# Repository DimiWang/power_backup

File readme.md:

# Power backup automation for 12V battery.

## Features:
* Fits on DIN rail.
* Power source circuit cut-off when no power
   (saves battery energy when power is not available)
* Measures battery real capacity
* Measures input voltage
* Battery cut-off when discharged
* LED signalisation
* Open collector signal on battery or power fail
* Output 5V max.100mA
* Output from battery
* Arduino pro mini
* Output bistable relay (for energy saving)

## Box enclosure

## Main Board

## Main Board TOP layer

## Main Board BOTTOM layer

## Main Board schematic

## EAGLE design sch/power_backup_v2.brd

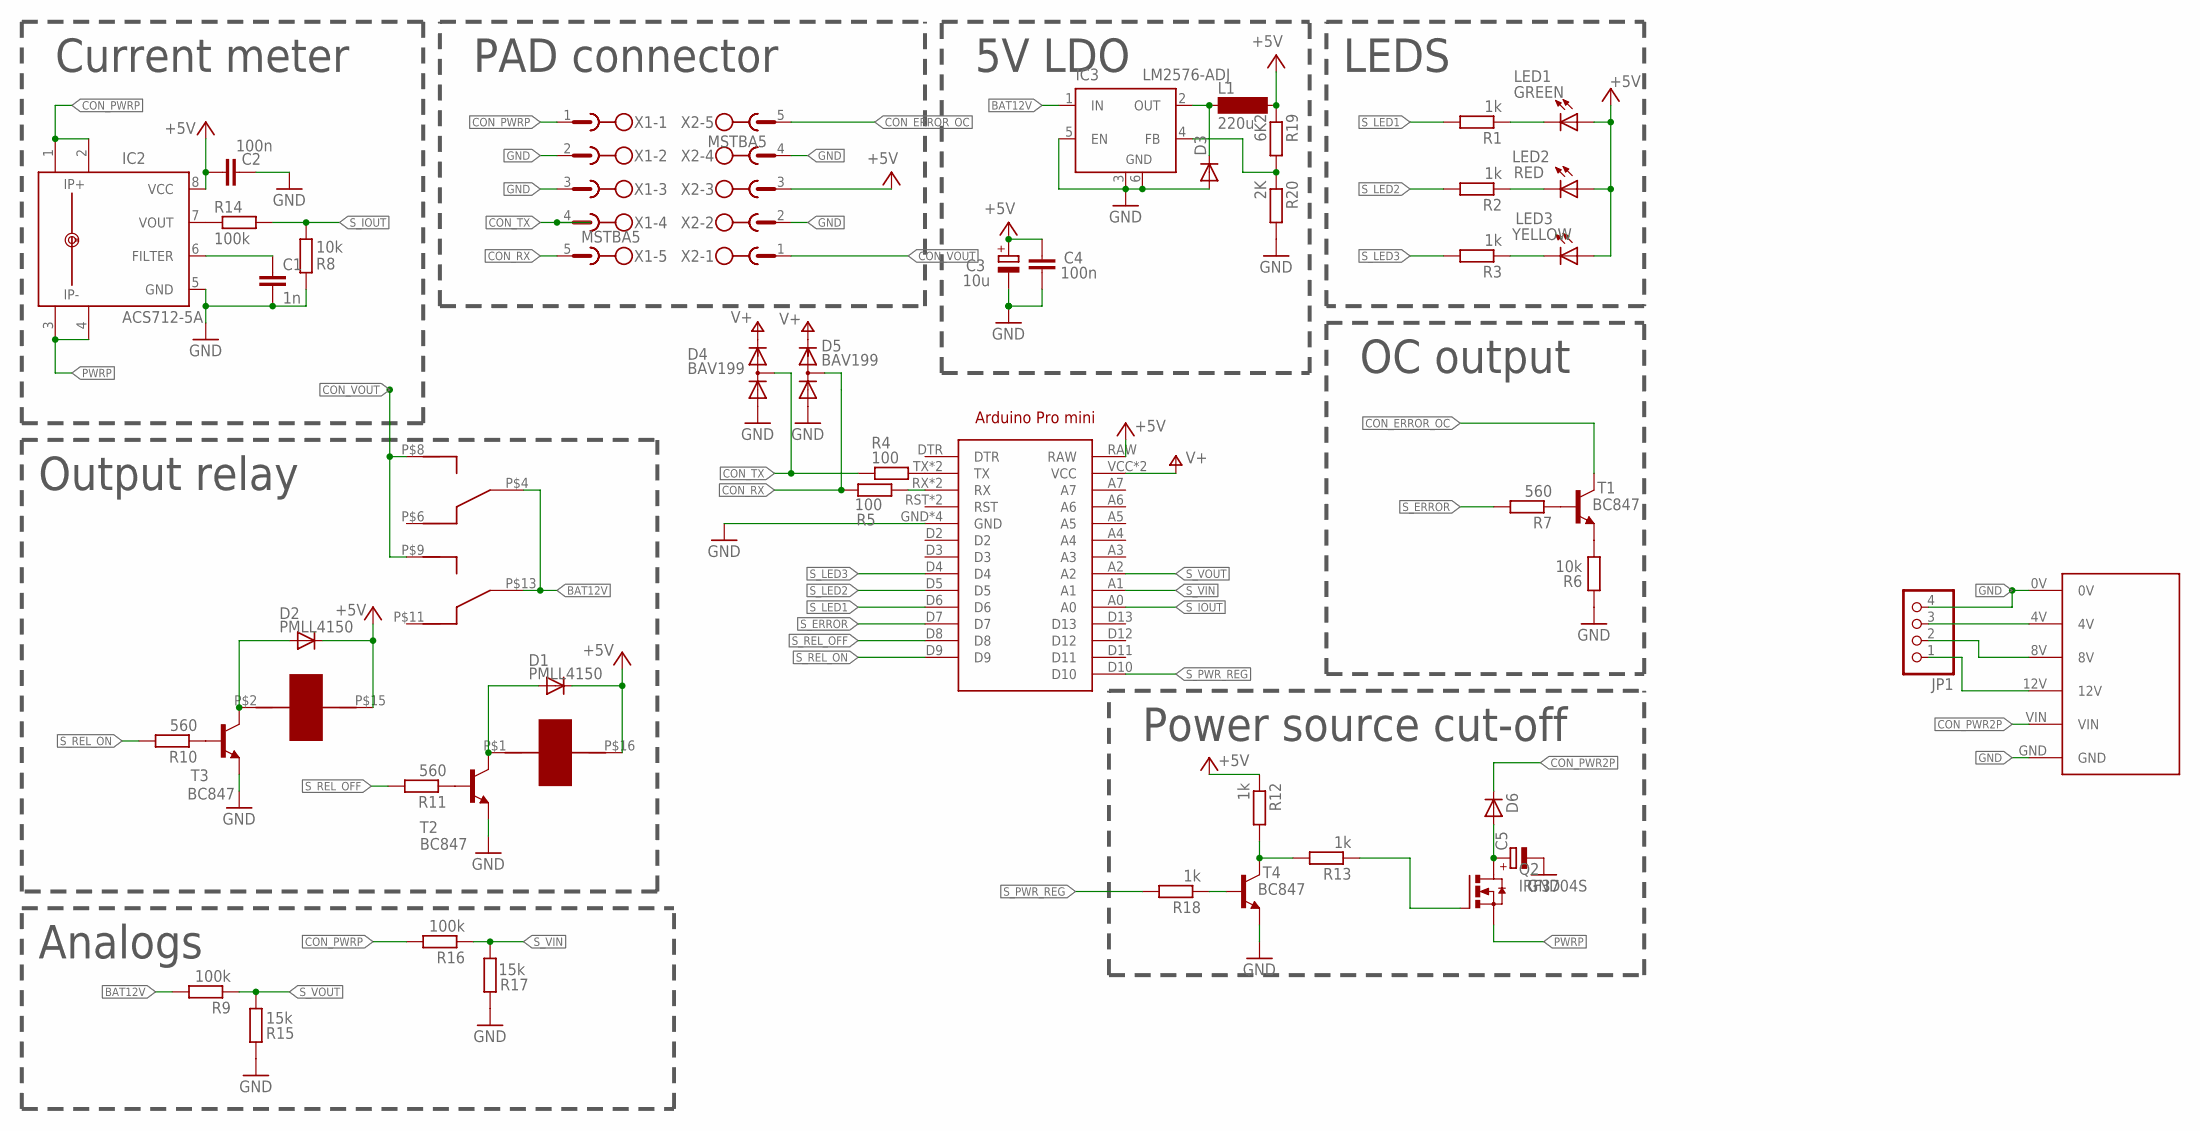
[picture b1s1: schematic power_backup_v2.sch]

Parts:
ARDUINO1: ARDUINO_PRO_MINI
C1: 1n; C0805
C2, C4: 100n; C0805
C3: 10u; SMC_C
C5: CPOL-EUE3.5-8; E3,5-8
D1, D2: PMLL4150; SOD80C
D3: DIODE-DO214AA; DO214AA
D4, D5: BAV199; SOT23
D6: DIODE_E-SMC; DIODE_SMC
IC2: ACS712-5A; SOIC8
IC3: LM2576-ADJ; TO263-5
JP1: PINHD-1X4; 1X04
K2: HFD2/003; RELAY
L1: 220u; MS85
LED1: GREEN; LED3MM
LED2: RED; LED3MM
LED3: YELLOW; LED3MM
Q2: IRF3704S; D2PACK
R1, R2, R3, R12, R13, R18: 1k; M0805
R4, R5: 100; M0805
R6, R8: 10k; M0805
R7, R10, R11: 560; M0805
R9, R14, R16: 100k; M0805
R15, R17: 15k; M0805
R19: 6K2; M0805
R20: 2K; M0805
T1, T2, T3, T4: BC847; SOT23
U$1: BALANCER
X1, X2: MSTBA5

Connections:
+5V: ARDUINO1.RAW, C2.1, C3.+, C4.1, D1.C, D2.C, IC2.8 (VCC), K2.P$15, K2.P$16, L1.2, LED1.A, LED2.A, LED3.A, R12.1, R19.1, X2.3
BAT4V: JP1.3, U$1.4V
BAT8V: JP1.2, U$1.8V
BAT12V: IC3.1 (IN), JP1.1, K2.P$4 (MID), K2.P$13 (MID), R9.2, U$1.12V
CON_ERROR_OC: T1.3 (C), X2.5
CON_PWR2P: D6.C (A), U$1.VIN
CON_PWRP: IC2.1 (IP+), IC2.2 (IP+1), R16.2, X1.1
CON_RX: D5.3 (AC), R5.1, X1.5
CON_TX: D4.3 (AC), R4.1, X1.4
CON_VOUT: K2.P$8 (NO), K2.P$9 (NO), X2.1
GND: ARDUINO1.GND, ARDUINO1.GND@1 (GND), ARDUINO1.GND@2 (GND), ARDUINO1.GND@3 (GND), C1.2, C2.2, C3.-, C4.2, C5.-, D3.A, D4.1 (A), D5.1 (A), IC2.5 (GND), IC3.3 (GND), IC3.5 (EN), IC3.6 (GND), JP1.4, R6.1, R8.2, R15.2, R17.2, R20.2, T2.2 (E), T3.2 (E), T4.2 (E), U$1.0V, U$1.GND, X1.2, X1.3, X2.2, X2.4
unnamed: LED1.K (C), R1.1
unnamed: LED2.K (C), R2.1
unnamed: LED3.K (C), R3.1
unnamed: C5.+, D6.A (C), Q2.2 (D)
unnamed: D1.A, K2.P$1, T2.3 (C)
unnamed: D2.A, K2.P$2, T3.3 (C)
unnamed: R10.1, T3.1 (B)
unnamed: R11.1, T2.1 (B)
unnamed: R12.2, R13.2, T4.3 (C)
unnamed: Q2.1 (G), R13.1
unnamed: C1.1, IC2.6 (FILTER)
unnamed: IC2.7 (VOUT), R14.1
unnamed: R7.1, T1.1 (B)
unnamed: R6.2, T1.2 (E)
unnamed: R18.1, T4.1 (B)
unnamed: ARDUINO1.TX, ARDUINO1.TX@1 (TX), R4.2
unnamed: ARDUINO1.RX, ARDUINO1.RX@1 (RX), R5.2
unnamed: D3.C, IC3.2 (OUT), L1.1
unnamed: IC3.4 (FB), R19.2, R20.1
PWRP: IC2.3 (IP-), IC2.4 (IP-1), Q2.3 (S)
S_ERROR: ARDUINO1.D7, R7.2
S_IOUT: ARDUINO1.A0, R8.1, R14.2
S_LED1: ARDUINO1.D6, R1.2
S_LED2: ARDUINO1.D5, R2.2
S_LED3: ARDUINO1.D4, R3.2
S_PWR_REG: ARDUINO1.D10, R18.2
S_REL_OFF: ARDUINO1.D8, R11.2
S_REL_ON: ARDUINO1.D9, R10.2
S_VIN: ARDUINO1.A1, R16.1, R17.1
S_VOUT: ARDUINO1.A2, R9.1, R15.1
V+: ARDUINO1.VCC, ARDUINO1.VCC@1 (VCC), D4.2 (C), D5.2 (C)

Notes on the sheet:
Output relay
Analogs
Current meter
PAD connector
LEDS
5V LDO
OC output
Power source cut-off

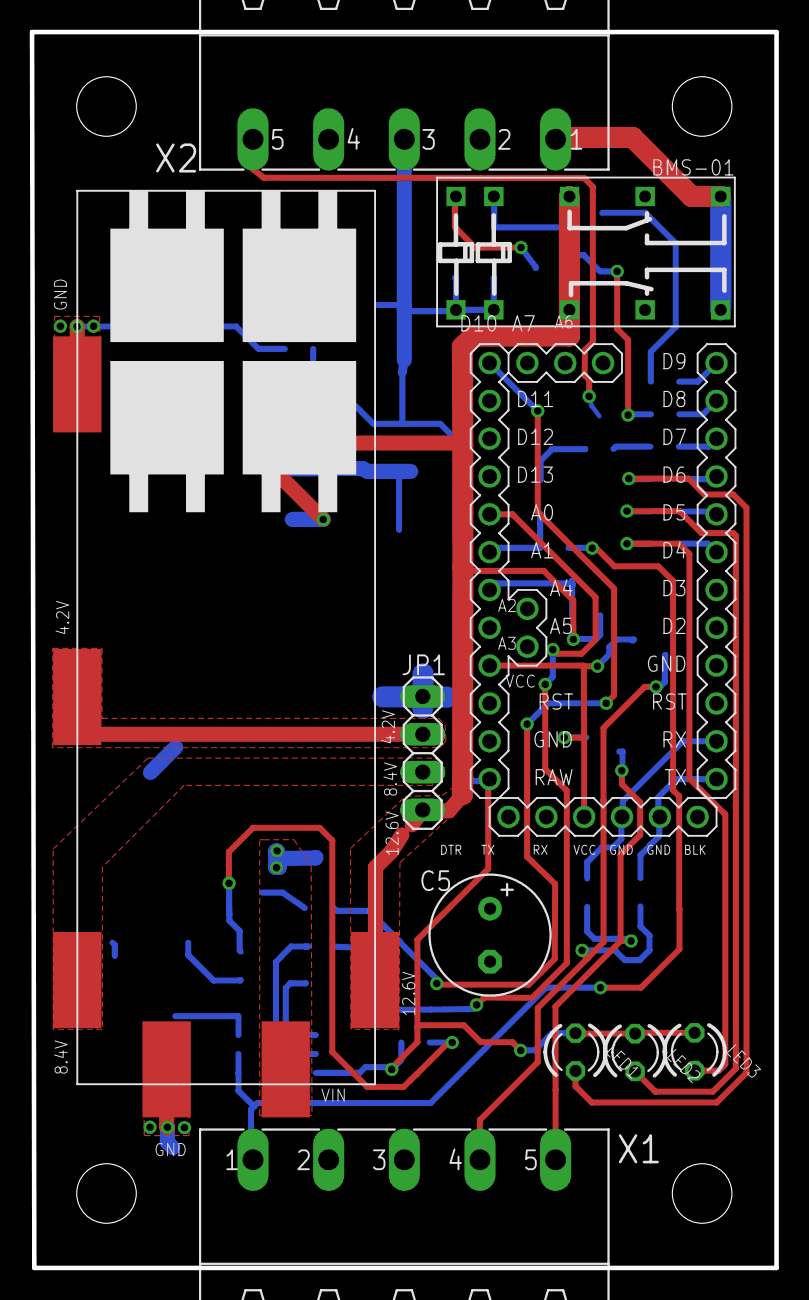
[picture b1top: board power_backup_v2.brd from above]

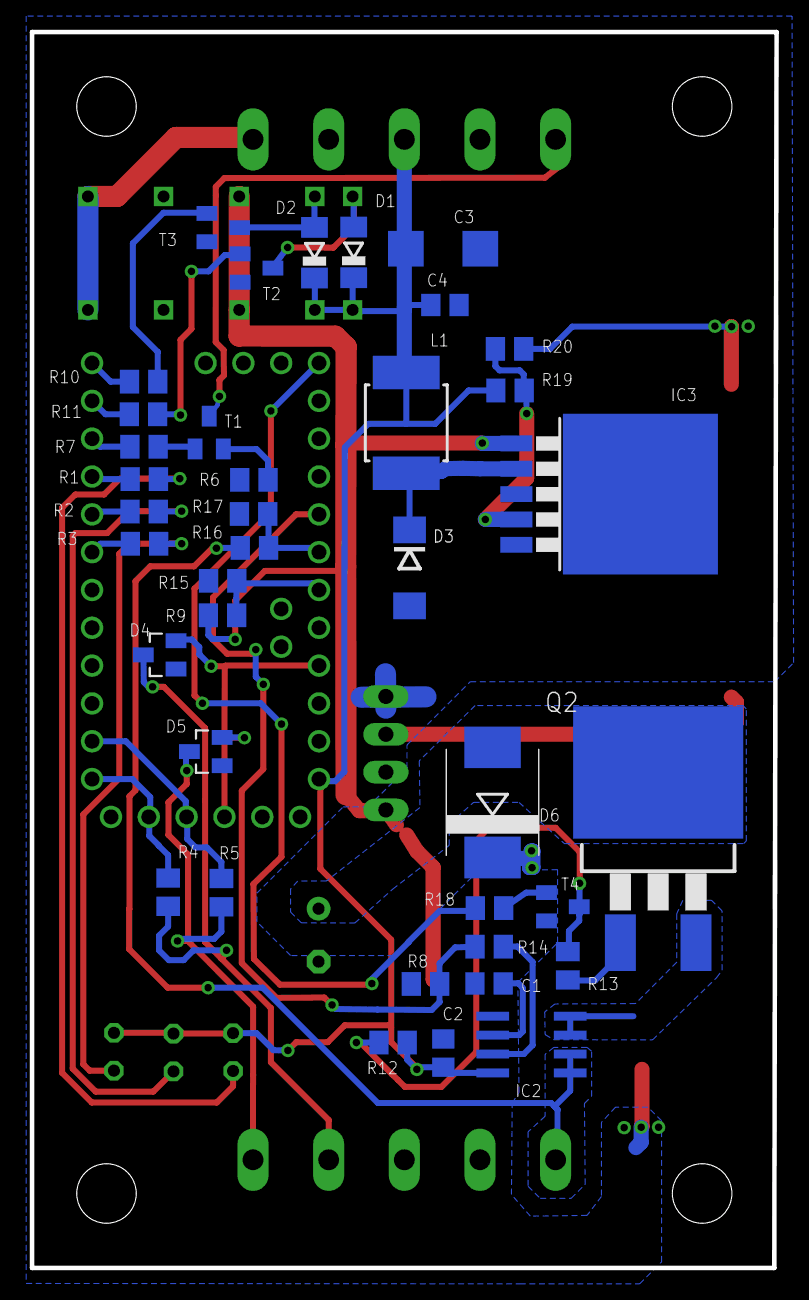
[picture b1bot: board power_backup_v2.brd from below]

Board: 2 copper layers, 50.0 x 83.0 mm, 48 parts (38 on the bottom side), 42 nets.

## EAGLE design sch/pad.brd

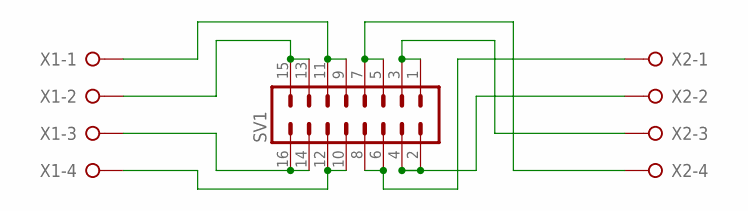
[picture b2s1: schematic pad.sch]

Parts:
SV1: MA08-2
X1, X2: W237-04P; W237-4P

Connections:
IN1: SV1.9, SV1.11, X1.1
IN2: SV1.13, SV1.15, X1.2
IN3: SV1.14, SV1.16, X1.3
IN4: SV1.10, SV1.12, X1.4
OUT1: SV1.6, SV1.8, X2.1
OUT2: SV1.2, SV1.4, X2.2
OUT3: SV1.1, SV1.3, X2.3
OUT4: SV1.5, SV1.7, X2.4

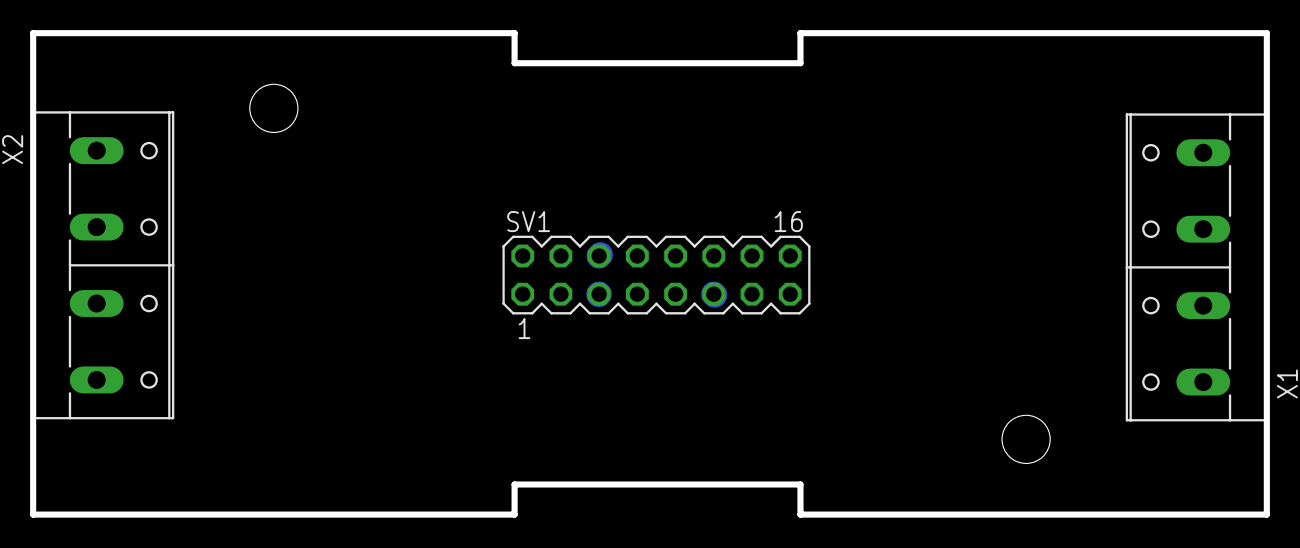
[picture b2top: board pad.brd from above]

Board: 2 copper layers, 82.0 x 32.0 mm, 3 parts (0 on the bottom side), 8 nets.

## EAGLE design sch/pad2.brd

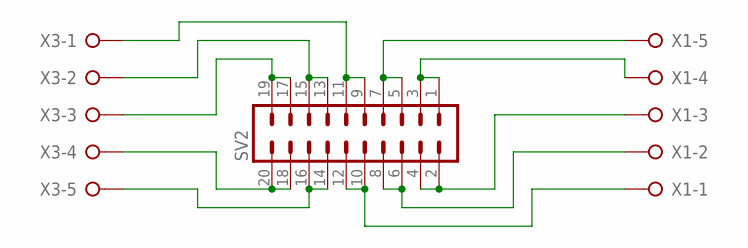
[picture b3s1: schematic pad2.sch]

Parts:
SV2: MA10-2
X1, X3: W237-05P; W237-5P

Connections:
IN1: SV2.13, SV2.15, X3.2
IN2: SV2.17, SV2.19, X3.3
IN3: SV2.18, SV2.20, X3.4
IN4: SV2.14, SV2.16, X3.5
unnamed: SV2.9, SV2.11, X3.1
unnamed: SV2.10, SV2.12, X1.1
OUT1: SV2.6, SV2.8, X1.2
OUT2: SV2.2, SV2.4, X1.3
OUT3: SV2.1, SV2.3, X1.4
OUT4: SV2.5, SV2.7, X1.5

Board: 2 copper layers, 3 parts (0 on the bottom side), 10 nets, no tracks yet.

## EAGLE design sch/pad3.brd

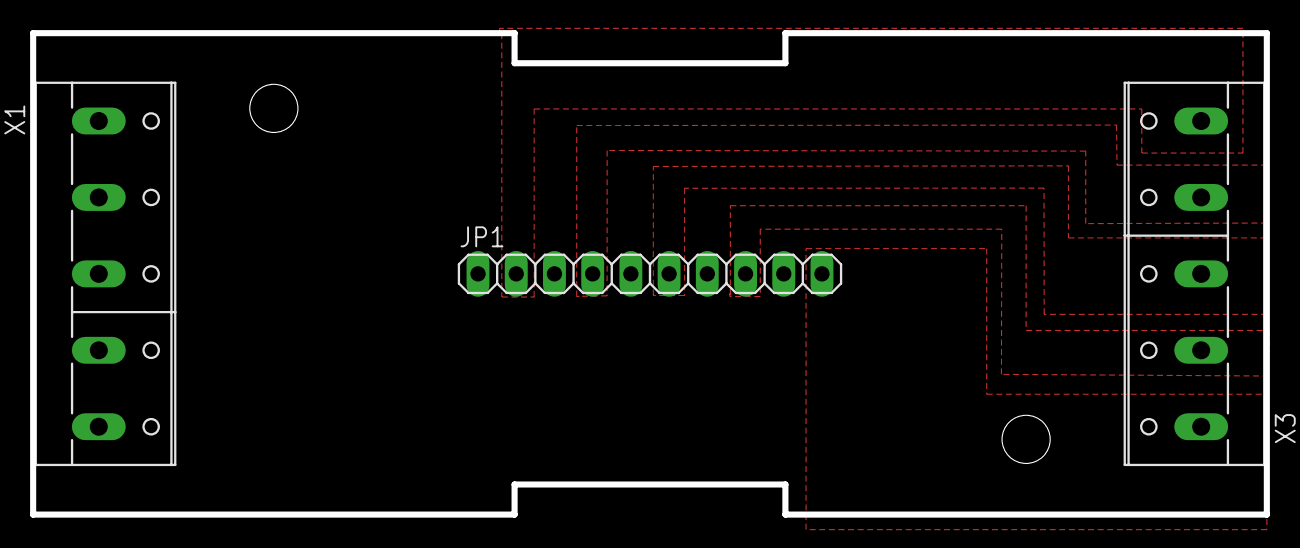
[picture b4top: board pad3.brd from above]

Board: 2 copper layers, 82.0 x 32.0 mm, 3 parts (0 on the bottom side), 10 nets, no tracks yet.

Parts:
JP1: 1X10
X1, X3: W237-5P

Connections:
unnamed: JP1.9, X1.1
unnamed: JP1.10, X3.1
unnamed: JP1.8, X3.2
unnamed: JP1.7, X1.2
unnamed: JP1.6, X3.3
unnamed: JP1.4, X3.4
unnamed: JP1.5, X1.3
unnamed: JP1.3, X1.4
unnamed: JP1.2, X3.5
unnamed: JP1.1, X1.5

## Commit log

2023-12-28 rename to pad and move terminals
2024-01-06 PCBs first version ordered
2024-01-06 Board pictures and readme.md added
2024-01-06 Enclosure image and schematic added
2024-01-17 code example added
2024-01-17 updated device image
2024-01-18 updated images
2024-01-23 updated diagram
2024-04-01 version 2
